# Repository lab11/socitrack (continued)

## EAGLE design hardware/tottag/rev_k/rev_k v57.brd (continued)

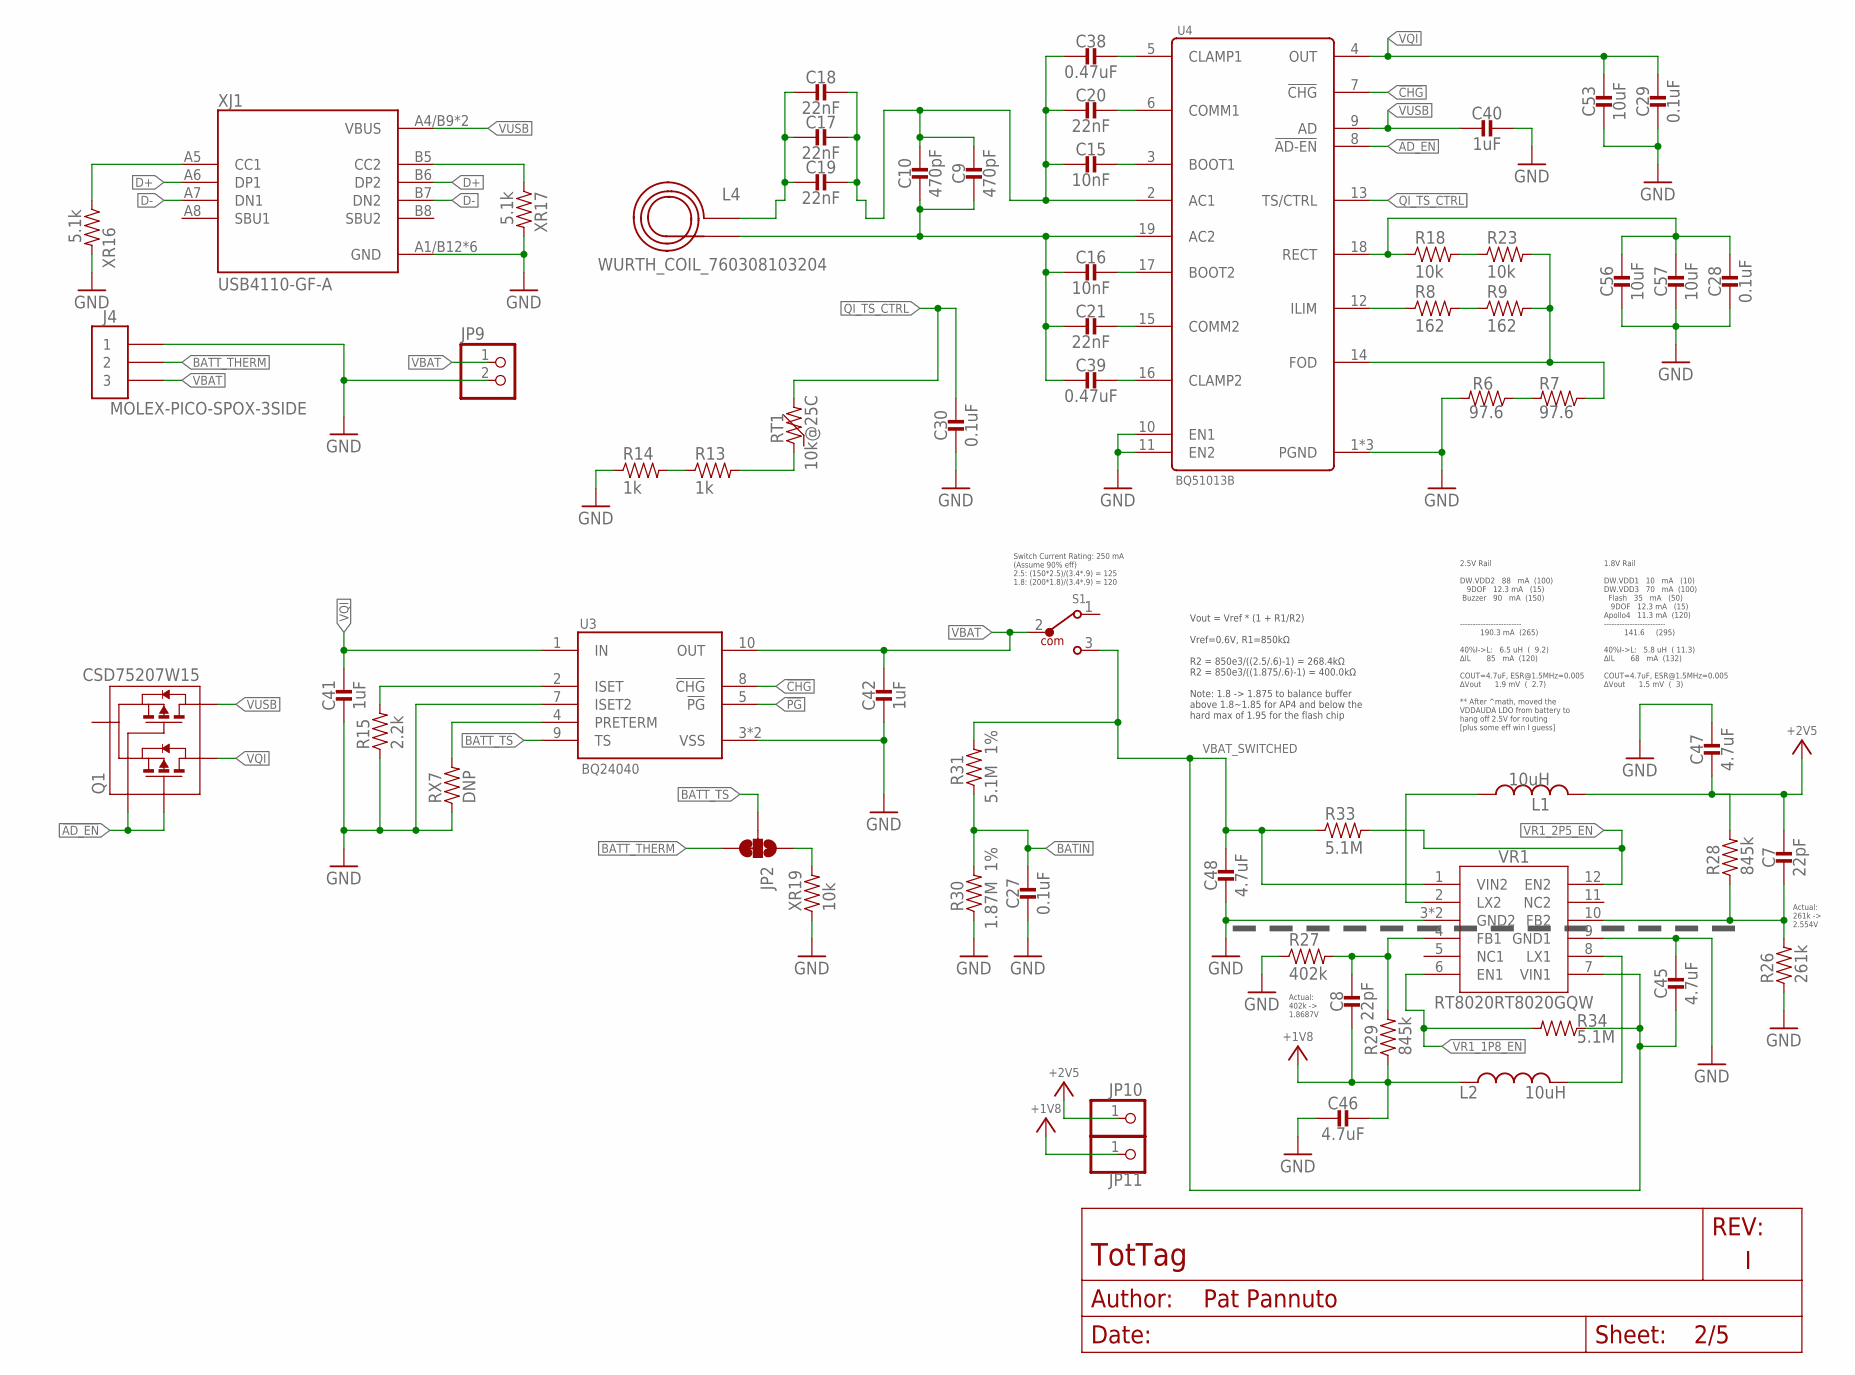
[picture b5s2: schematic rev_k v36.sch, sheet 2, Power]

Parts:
C7, C8: 22pF; 0201_CAP; MPN GRM0335C1H220FA01D
C9, C10: 470pF; 0402_CAP; MPN GRM1555C1H471JA01J; DIGIKEY 490-6242-1-ND
C15, C16: 10nF; 0402_CAP; MPN GRM155R71H103KA88J; DIGIKEY 490-6351-2-ND
C17, C18, C19: 22nF; 0402_CAP; MPN GRM155R71E223JA61D; DIGIKEY 490-10699-2-ND
C20, C21: 22nF; 0402_CAP; MPN CC0402ZRY5V8BB223; DIGIKEY 311-3823-1-ND
C27, C28, C29, C30: 0.1uF; 0402_CAP; MPN GRM155R71C104KA88J; DIGIKEY 490-6328-1-ND
C38, C39: 0.47uF; 0402_CAP; MPN GRT155R61E474ME01D; DIGIKEY 490-12270-1-ND
C40, C41, C42: 1uF; 0402_CAP; MPN GRM155R70J105KA12J
C45, C46, C47, C48: 4.7uF; 0603_CAP; MPN C1608X7S1A475K080AC
C53, C56, C57: 10uF; 0603_CAP; MPN CM105X5R106M25AT; DIGIKEY 1253-CM105X5R106M25ATCT-ND
J4: MOLEX-PICO-SPOX-3SIDE; MOLEX-PICO-SPOX-3_SIDE
JP2: JUMPER-SMT_3_1-NC_TRACE_SILK; SMT-JUMPER_3_1-NC_TRACE_SILK
JP9: PINHD-1X2; 1X02
JP10, JP11: PINHD-1X1; 1X01
L1, L2: 10uH; NRX3015; MPN NR3015T100M
L4: WURTH_COIL_760308103204
Q1: CSD75207W15; DSBGA
R6, R7: 97.6; 0402_RES; MPN RMCF0402FT97R6; DIGIKEY RMCF0402FT97R6CT-ND
R8, R9: 162; 0402_RES; MPN RMCF0402FT162R; DIGIKEY RMCF0402FT162RCT-ND
R13, R14: 1k; 0402_RES
R15: 2.2k; 0402_RES; MPN RMCF0402JT2K20; DIGIKEY RMCF0402JT2K20CT-ND
R18, R23: 10k; 0402_RES; MPN RC0402JR-0710KL; DIGIKEY 311-10KJRCT-ND
R26: 261k; 0201_RES; MPN ERJ-1GNF2613C
R27: 402k; 0201_RES; MPN ERJ-1GNF4023C
R28, R29: 845k; 0201_RES; MPN ERJ-1GNF8453C
R30: 1.87M; 0402_RES; TOLERANCE 1%; MPN RMCF0402FT1M87
R31: 5.1M; 0402_RES; TOLERANCE 1%; MPN RMCF0402FT5M10; DIGIKEY RMCF0402FT5M10CT-ND
R33, R34: 5.1M; 0402_RES; MPN RMCF0402FT5M10; DIGIKEY RMCF0402FT5M10CT-ND
RT1: 10k@25C; 0402_RES; MPN NCU15XH103F60RC; DIGIKEY 490-18149-1-ND
RX7: DNP; 0402_RES
S1: 450404015514; DIGIKEY 732-13665-1-ND
U3: BQ24040; DSQ0010A
U4: BQ51013B; RHL0020A
VR1: RT8020RT8020GQW; SON45P300X300X80-13T160X250N
XJ1: USB4110-GF-A; GCT_USB4110-GF-A
XR16, XR17: 5.1k; 0402_RES; MPN RMCF0402FT5K10; DIGIKEY RMCF0402FT5K10CT-ND
XR19: 10k; 0402_RES; MPN RC0402JR-0710KL; DIGIKEY 311-10KJRCT-ND

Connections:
!AD_EN: Q1.A1 (G1), Q1.C1 (G2), U4.8 (!AD-EN)
!CHG: U3.8 (!CHG), U4.7 (!CHG); also elsewhere on the board
!PG: U3.5 (!PG); also elsewhere on the board
+1V8: C8.P$2 (2), C46.1, JP11.1, L2.P$1 (1), R29.1; also elsewhere on the board
+2V5: C7.P$1 (1), C47.2, JP10.1, L1.P$2 (2), R28.2; also elsewhere on the board
BATIN: C27.1, R30.2, R31.1; also elsewhere on the board
BATT_THERM: J4.2, J4.2SUPP (2), JP2.3
BATT_TS: JP2.2, U3.9 (TS)
BQ_AC1: C9.1, C10.1, C15.2, C17.1, C18.1, C19.1, C20.2, C38.2, U4.2 (AC1)
BQ_AC2: C9.2, C10.2, C16.2, C21.2, C39.2, L4.P$2 (2), U4.19 (AC2)
BQ_BOOT1: C15.1, U4.3 (BOOT1)
BQ_BOOT2: C16.1, U4.17 (BOOT2)
BQ_CLAMP1: C38.1, U4.5 (CLAMP1)
BQ_CLAMP2: C39.1, U4.16 (CLAMP2)
BQ_COMM1: C20.1, U4.6 (COMM1)
BQ_COMM2: C21.1, U4.15 (COMM2)
BQ_FOD: R7.1, R9.2, R23.2, U4.14 (FOD)
BQ_ILM: R8.1, U4.12 (ILIM)
BQ_ISET: R15.2, U3.2 (ISET)
BQ_RECT: C28.1, C56.1, C57.1, R18.1, U4.18 (RECT)
COIL_AC1: C17.2, C18.2, C19.2, L4.P$1 (1)
D+: XJ1.A6 (DP1), XJ1.B6 (DP2)
D-: XJ1.A7 (DN1), XJ1.B7 (DN2)
GND: C27.2, C28.2, C29.2, C30.2, C40.1, C41.2, C42.2, C45.1, C46.2, C47.1, C48.2, C53.2, C56.2, C57.2, J4.1, J4.1SUPP (1), JP9.2, R6.2, R14.1, R15.1, R26.1, R27.1, R30.1, RX7.1, U3.3 (VSS), U3.7 (ISET2), U3.PAD (VSS), U4.1 (PGND), U4.10 (EN1), U4.11 (EN2), U4.20 (PGND), U4.PAD (PGND), VR1.3 (GND2), VR1.9 (GND1), VR1.13 (GND2), XJ1.A1/B12 (GND), XJ1.B1/A12 (GND), XJ1.S1 (GND), XJ1.S2 (GND), XJ1.S3 (GND), XJ1.S4 (GND), XR16.2, XR17.2, XR19.1; also elsewhere on the board
unnamed: XJ1.B5 (CC2), XR17.1
unnamed: XJ1.A5 (CC1), XR16.1
unnamed: R6.1, R7.2
unnamed: JP2.1, XR19.2
unnamed: RX7.2, U3.4 (PRETERM)
unnamed: R18.2, R23.1
unnamed: R8.2, R9.1
unnamed: R13.2, RT1.1
unnamed: R13.1, R14.2
QI_TS_CTRL: C30.1, RT1.2, U4.13 (TS/CTRL); also elsewhere on the board
VBAT: C42.1, J4.3, J4.3SUPP (3), JP9.1, S1.2, U3.10 (OUT)
VBAT_SWITCHED: C45.2, C48.1, R31.2, R33.1, R34.1, S1.3, VR1.1 (VIN2), VR1.7 (VIN1); also elsewhere on the board
VQI: C29.1, C41.1, C53.1, Q1.A2 (D1), Q1.A3 (D1), Q1.B3 (D1), U3.1 (IN), U4.4 (OUT)
VR1_1P8_EN: R34.2, VR1.6 (EN1)
VR1_2P5_EN: R33.2, VR1.12 (EN2)
VR1_FB1: C8.P$1 (1), R27.2, R29.2, VR1.4 (FB1)
VR1_FB2: C7.P$2 (2), R26.2, R28.1, VR1.10 (FB2)
VR1_LX1: L2.P$2 (2), VR1.8 (LX1)
VR1_LX2: L1.P$1 (1), VR1.2 (LX2)
VUSB: C40.2, Q1.B2 (D2), Q1.C2 (D2), Q1.C3 (D2), U4.9 (AD), XJ1.A4/B9 (VBUS), XJ1.B4/A9 (VBUS)

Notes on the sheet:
2.5V Rail DW.VDD2 88 mA (100) 9DOF 12.3 mA (15) Buzzer 90 mA (150) ------------------------ 190.3 mA (265) 40%I->L: 6.5 uH ( 9.2) ∆IL 85 mA (120) COUT=4.7uF, ESR@1.5MHz=0.005 ∆Vout 1.9 mV ( 2.7) ** After ^math, moved the VDDAUDA LDO from battery to hang off 2.5V for routing [plus some eff win I gue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
1.8V Rail DW.VDD1 10 mA (10) DW.VDD3 70 mA (100) Flash 35 mA (50) 9DOF 12.3 mA (15) Apollo4 11.3 mA (120) ------------------------ 141.6 (295) 40%I->L: 5.8 uH ( 11.3) ∆IL 68 mA (132) COUT=4.7uF, ESR@1.5MHz=0.005 ∆Vout 1.5 mV ( 3)
Vout = Vref * (1 + R1/R2) Vref=0.6V, R1=850kΩ R2 = 850e3/((2.5/.6)-1) = 268.4kΩ R2 = 850e3/((1.875/.6)-1) = 400.0kΩ Note: 1.8 -> 1.875 to balance buffer above 1.8~1.85 for AP4 and below the hard max of 1.95 for the flash chip
Switch Current Rating: 250 mA (Assume 90% eff) 2.5: (150*2.5)/(3.4*.9) = 125 1.8: (200*1.8)/(3.4*.9) = 120
Actual: 402k -> 1.8687V
Actual: 261k -> 2.554V

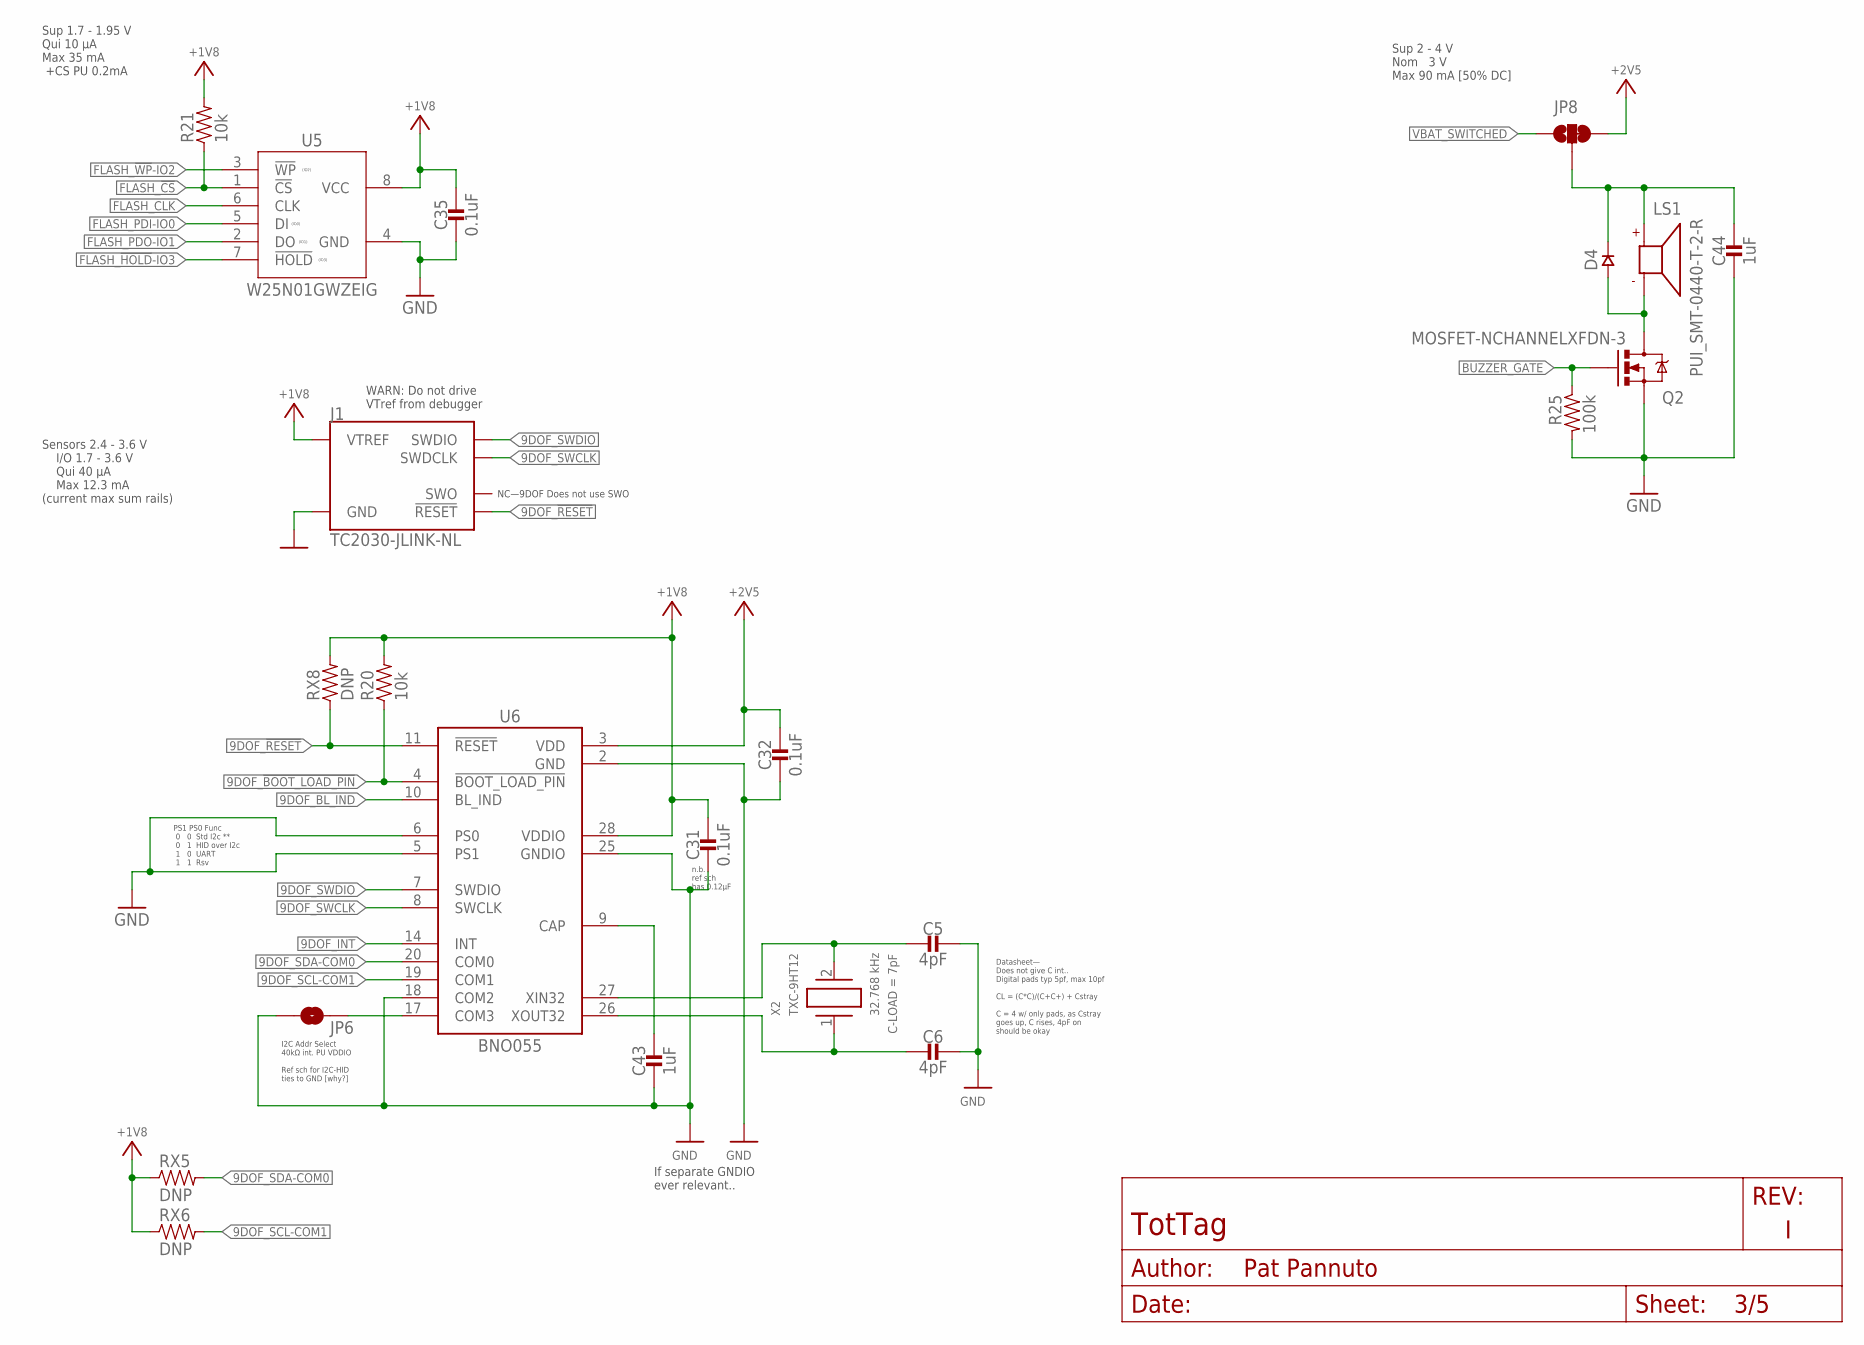
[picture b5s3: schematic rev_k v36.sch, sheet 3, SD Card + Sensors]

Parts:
C5, C6: 4pF; 0201_CAP; MPN GRM0335C1H4R0BA01D
C31, C32, C35: 0.1uF; 0402_CAP; MPN CL05A104KP5NNNC
C43, C44: 1uF; 0402_CAP; MPN GRM155R70J105KA12J
D4: DIODE0402; 0402_DIODE; MPN CDSQR400B-HF; DIGIKEY 641-2087-1-ND
J1: TC2030-JLINK-NL; TC2030-IDC-NL
JP6: JUMPER-SMT_2_NO_SILK; SMT-JUMPER_2_NO_SILK
JP8: JUMPER-SMT_3_1-NC_TRACE_SILK; SMT-JUMPER_3_1-NC_TRACE_SILK
LS1: PUI_SMT-0440-T-2-R; SMT-0440-T-2-R
Q2: MOSFET-NCHANNELXFDN-3; XFDFN-3
R20, R21: 10k; 0402_RES; MPN RC0402JR-0710KL; DIGIKEY 311-10KJRCT-ND
R25: 100k; 0402_RES; MPN RT0402BRE07100KL
RX5, RX6, RX8: DNP; 0603-RES
U5: W25N01GWZEIG; WSON127P800X600X80-9T430X340N
U6: BNO055; LGA28R0P510X4_5P2X3P8X1
X2: TXC-9HT12; MPN 9HT12-32.768KDZY-T

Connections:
9DOF_!BOOT_LOAD_PIN: R20.1, U6.4 (!BOOT_LOAD_PIN); also elsewhere on the board
9DOF_!RESET: J1.3 (!RESET), RX8.1, U6.11 (!RESET); also elsewhere on the board
9DOF_BL_IND: U6.10 (BL_IND); also elsewhere on the board
9DOF_CAP: C43.1, U6.9 (CAP)
9DOF_INT: U6.14 (INT); also elsewhere on the board
9DOF_SCL-COM1: RX6.2, U6.19 (COM1); also elsewhere on the board
9DOF_SDA-COM0: RX5.2, U6.20 (COM0); also elsewhere on the board
9DOF_SWCLK: J1.4 (SWDCLK), U6.8 (SWCLK)
9DOF_SWDIO: J1.2 (SWDIO), U6.7 (SWDIO)
9DOF_XI: C5.P$2 (2), U6.27 (XIN32), X2.2
9DOF_XO: C6.P$2 (2), U6.26 (XOUT32), X2.1
+1V8: C31.1, C35.1, J1.1 (VTREF), R20.2, R21.2, RX5.1, RX6.1, RX8.2, U5.8 (VCC), U6.28 (VDDIO); also elsewhere on the board
+2V5: C32.1, JP8.3, U6.3 (VDD); also elsewhere on the board
BUZZER_GATE: Q2.G, R25.1; also elsewhere on the board
BUZZER_SUPPLY: C44.1, D4.CATHODE, JP8.2, LS1.+
FLASH_!CS: R21.1, U5.1 (!CS); also elsewhere on the board
FLASH_!HOLD!-IO3: U5.7 (!HOLD); also elsewhere on the board
FLASH_!WP!-IO2: U5.3 (!WP); also elsewhere on the board
FLASH_CLK: U5.6 (CLK); also elsewhere on the board
FLASH_PDI-IO0: U5.5 (DI); also elsewhere on the board
FLASH_PDO-IO1: U5.2 (DO); also elsewhere on the board
GND: C5.P$1 (1), C6.P$1 (1), C31.2, C32.2, C35.2, C43.2, C44.2, J1.5 (GND), JP6.1, Q2.S, R25.2, U5.4 (GND), U6.2 (GND), U6.5 (PS1), U6.6 (PS0), U6.18 (COM2), U6.25 (GNDIO); also elsewhere on the board
unnamed: D4.ANODE, LS1.- (N), Q2.D
unnamed: JP6.2, U6.17 (COM3)
VBAT_SWITCHED: JP8.1; also elsewhere on the board

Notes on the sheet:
Sup 1.7 - 1.95 V Qui 10 µA Max 35 mA +CS PU 0.2mA
Sensors 2.4 - 3.6 V I/O 1.7 - 3.6 V Qui 40 µA Max 12.3 mA (current max sum rails)
Sup 2 - 4 V Nom 3 V Max 90 mA [50% DC]
PS1 PS0 Func 0 0 Std I2c ** 0 1 HID over I2c 1 0 UART 1 1 Rsv
If separate GNDIO ever relevant..
I2C Addr Select 40kΩ int. PU VDDIO Ref sch for I2C-HID ties to GND [why?]
n.b. ref sch has 0.12µF
WARN: Do not drive VTref from debugger
Datasheet— Does not give C int.. Digital pads typ 5pf, max 10pf CL = (C*C)/(C+C+) + Cstray C = 4 w/ only pads, as Cstray goes up, C rises, 4pF on should be okay
NC—9DOF Does not use SWO

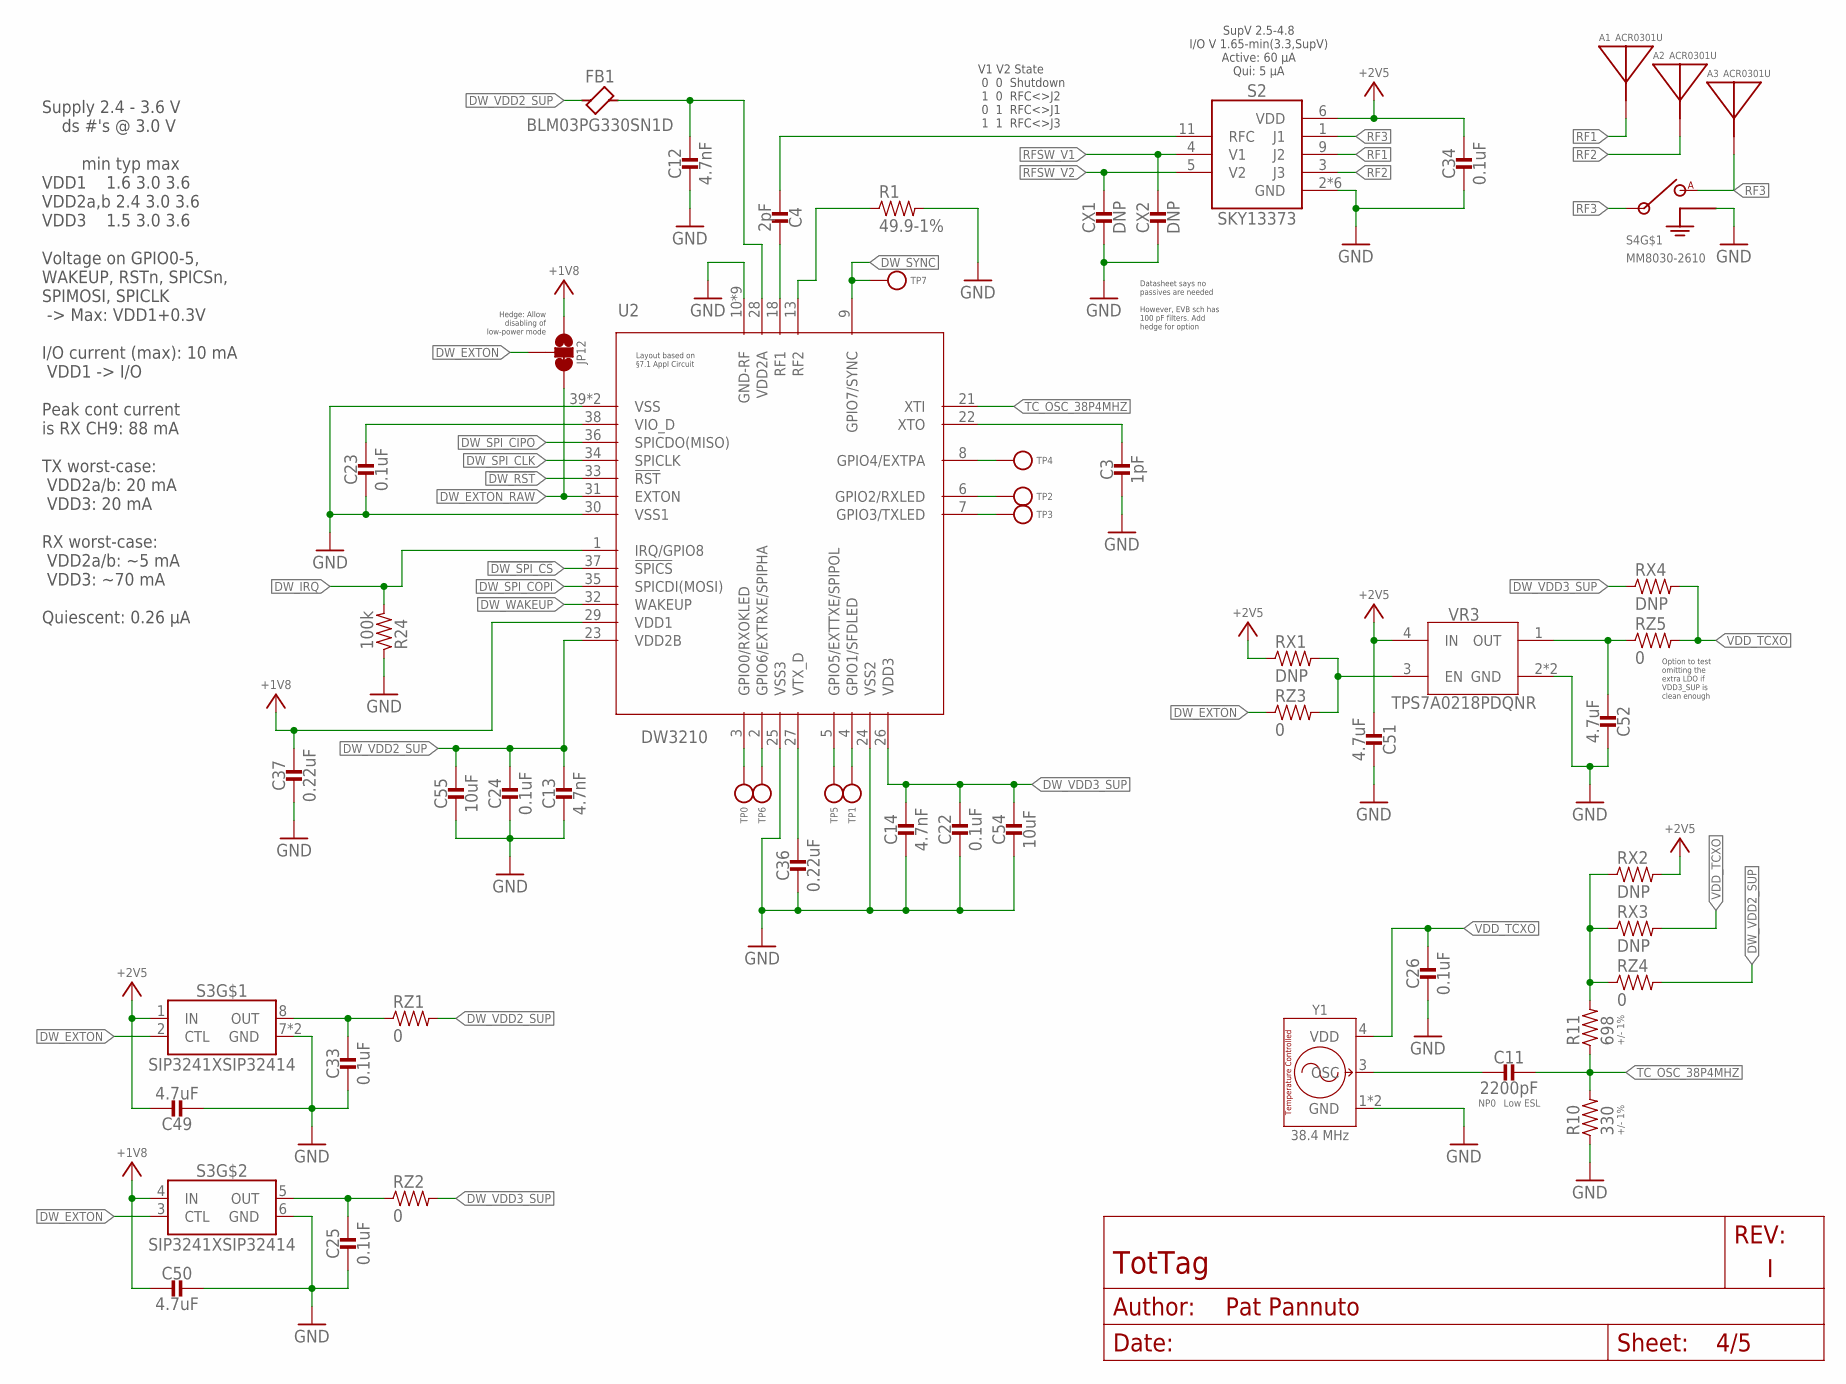
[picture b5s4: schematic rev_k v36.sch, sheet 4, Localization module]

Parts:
A1, A2, A3: ACR0301U
C3: 1pF; 0603_CAP; MPN C0603C109C5GACAUTO
C4: 2pF; 0201_CAP; MPN CBR02C209A5GAC
C11: 2200pF; 0603_CAP; MPN C0603C222F3GEC7867
C12, C13, C14: 4.7nF; 0402_CAP; MPN C0402C472K3RAC7867
C22, C23, C24, C25, C26, C33, C34: 0.1uF; 0402_CAP; MPN CL05A104KP5NNNC
C36, C37: 0.22uF; 0402_CAP; MPN CL05A224KP5NNNC
C49, C50, C51, C52: 4.7uF; 0603_CAP; MPN C1608X7S1A475K080AC
C54, C55: 10uF; 0603_CAP; MPN CM105X5R106M25AT; DIGIKEY 1253-CM105X5R106M25ATCT-ND
CX1, CX2: DNP; 0603_CAP
FB1: BLM03PG330SN1D; 0201_FB; MPN BLM03PG330SN1D
JP12: JUMPER-SMT_3_1-NC_TRACE_SILK; SMT-JUMPER_3_1-NC_TRACE_SILK
R1: 49.9-1%; 0201_RES; MPN ERJ-1GNF49R9C
R10: 330; 0603-RES; TOLERANCE +/- 1%; MPN RC0805FR-13330RL
R11: 698; 0603-RES; TOLERANCE +/- 1%; MPN RC0805FR-07698RL
R24: 100k; 0402_RES; MPN RT0402BRE07100KL
RX1, RX2, RX3, RX4: DNP; 0603-RES
RZ1, RZ2, RZ3, RZ4, RZ5: 0; 0603-RES; MPN RMCF0603ZT0R00
S2: SKY13373
S3: SIP3241XSIP32414; TDFN2X2X0P6-8
S4: MM8030-2610
TP0, TP1, TP2, TP3, TP4, TP5, TP6, TP7: TEST-POINT; PAD.03X.03
U2: DW3210; QFN40P500X500X80-40N
VR3: TPS7A0218PDQNR; 4-XDFN-EP
Y1: 38.4 MHz; OSCCC200X160X80; MPN O 38,40-JT21G-E-M-1,8-LF

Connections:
!DW_RST: U2.33 (!RST); also elsewhere on the board
!DW_SPI_CS: U2.37 (!SPICS); also elsewhere on the board
+1V8: C37.1, C50.2, JP12.1, S3.4 (IN), U2.29 (VDD1); also elsewhere on the board
+2V5: C34.1, C49.1, C51.2, RX1.1, RX2.2, S2.6 (VDD), S3.1 (IN), VR3.4 (IN); also elsewhere on the board
DW_EXTON: JP12.2, RZ3.1, S3.2 (CTL), S3.3 (CTL)
DW_EXTON_RAW: JP12.3, U2.31 (EXTON)
DW_GPIO4: TP4.P$1, U2.8 (GPIO4/EXTPA)
DW_GPIO5: TP5.P$1, U2.5 (GPIO5/EXTTXE/SPIPOL)
DW_GPIO6: TP6.P$1, U2.2 (GPIO6/EXTRXE/SPIPHA)
DW_IRQ: R24.2, U2.1 (IRQ/GPIO8); also elsewhere on the board
DW_RF1: C4.P$1 (1), U2.18 (RF1)
DW_RF2: R1.1, U2.13 (RF2)
DW_RXLED: TP2.P$1, U2.6 (GPIO2/RXLED)
DW_RXOKLED: TP0.P$1, U2.3 (GPIO0/RXOKLED)
DW_SFDLED: TP1.P$1, U2.4 (GPIO1/SFDLED)
DW_SPI_CIPO: U2.36 (SPICDO(MISO)); also elsewhere on the board
DW_SPI_CLK: U2.34 (SPICLK); also elsewhere on the board
DW_SPI_COPI: U2.35 (SPICDI(MOSI)); also elsewhere on the board
DW_SYNC: TP7.P$1, U2.9 (GPIO7/SYNC)
DW_TXLED: TP3.P$1, U2.7 (GPIO3/TXLED)
DW_VDD2A: C12.1, FB1.P$2, U2.28 (VDD2A)
DW_VDD2_PWROUT: C33.1, RZ1.1, S3.8 (OUT)
DW_VDD2_SUP: C13.1, C24.1, C55.1, FB1.P$1, RZ1.2, RZ4.2, U2.23 (VDD2B)
DW_VDD3_PWROUT: C25.1, RZ2.1, S3.5 (OUT)
DW_VDD3_SUP: C14.1, C22.1, C54.1, RX4.1, RZ2.2, U2.26 (VDD3)
DW_VIO_D: C23.1, U2.38 (VIO_D)
DW_VTX_D: C36.1, U2.27 (VTX_D)
DW_WAKEUP: U2.32 (WAKEUP); also elsewhere on the board
DW_XTO: C3.1, U2.22 (XTO)
GND: C3.2, C12.2, C13.2, C14.2, C22.2, C23.2, C24.2, C25.2, C26.2, C33.2, C34.2, C36.2, C37.2, C49.2, C50.1, C51.1, C52.1, C54.2, C55.2, CX1.2, CX2.2, R1.2, R10.1, R24.1, S2.2 (GND), S2.7 (GND), S2.8 (GND), S2.10 (GND), S2.12 (GND), S2.PAD (GND), S3.6 (GND), S3.7 (GND), S3.PAD (GND), S4.G1 (GND), S4.G2 (GND), U2.10 (GND-RF), U2.11 (GND-RF), U2.12 (GND-RF), U2.14 (GND-RF), U2.15 (GND-RF), U2.16 (GND-RF), U2.17 (GND-RF), U2.19 (GND-RF), U2.20 (GND-RF), U2.24 (VSS2), U2.25 (VSS3), U2.30 (VSS1), U2.39 (VSS), U2.40 (VSS), VR3.2 (GND), VR3.PAD (GND), Y1.1 (GND), Y1.2 (GND); also elsewhere on the board
RF1: A1.FEED, S2.9 (J2)
RF2: A2.FEED, S2.3 (J3)
RF3: A3.FEED, S2.1 (J1), S4.IN, S4.OUT (A)
RFC: C4.P$2 (2), S2.11 (RFC)
RFSW_V1: CX2.1, S2.4 (V1); also elsewhere on the board
RFSW_V2: CX1.1, S2.5 (V2); also elsewhere on the board
TCXO_BIAS_SUPP: R11.2, RX2.1, RX3.1, RZ4.1
TCXO_OUT: C11.2, Y1.3 (OSC)
TCXO_REG_EN: RX1.2, RZ3.2, VR3.3 (EN)
TCXO_REG_OUT: C52.2, RZ5.1, VR3.1 (OUT)
TC_OSC_38P4MHZ: C11.1, R10.2, R11.1, U2.21 (XTI)
VDD_TCXO: C26.1, RX3.2, RX4.2, RZ5.2, Y1.4 (VDD)

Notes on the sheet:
Supply 2.4 - 3.6 V ds #'s @ 3.0 V min typ max VDD1 1.6 3.0 3.6 VDD2a,b 2.4 3.0 3.6 VDD3 1.5 3.0 3.6 Voltage on GPIO0-5, WAKEUP, RSTn, SPICSn, SPIMOSI, SPICLK -> Max: VDD1+0.3V I/O current (max): 10 mA VDD1 -> I/O Peak cont current is RX CH9: 88 mA TX worst-case: VDD2a/b: 20 mA VDD3: 20 mA RX worst-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
SupV 2.5-4.8 I/O V 1.65-min(3.3,SupV) Active: 60 µA Qui: 5 µA
V1 V2 State 0 0 Shutdown 1 0 RFC<>J2 0 1 RFC<>J1 1 1 RFC<>J3
Datasheet says no passives are needed However, EVB sch has 100 pF filters. Add hedge for option
Hedge: Allow disabling of low-power mode
Option to test omitting the extra LDO if VDD3_SUP is clean enough

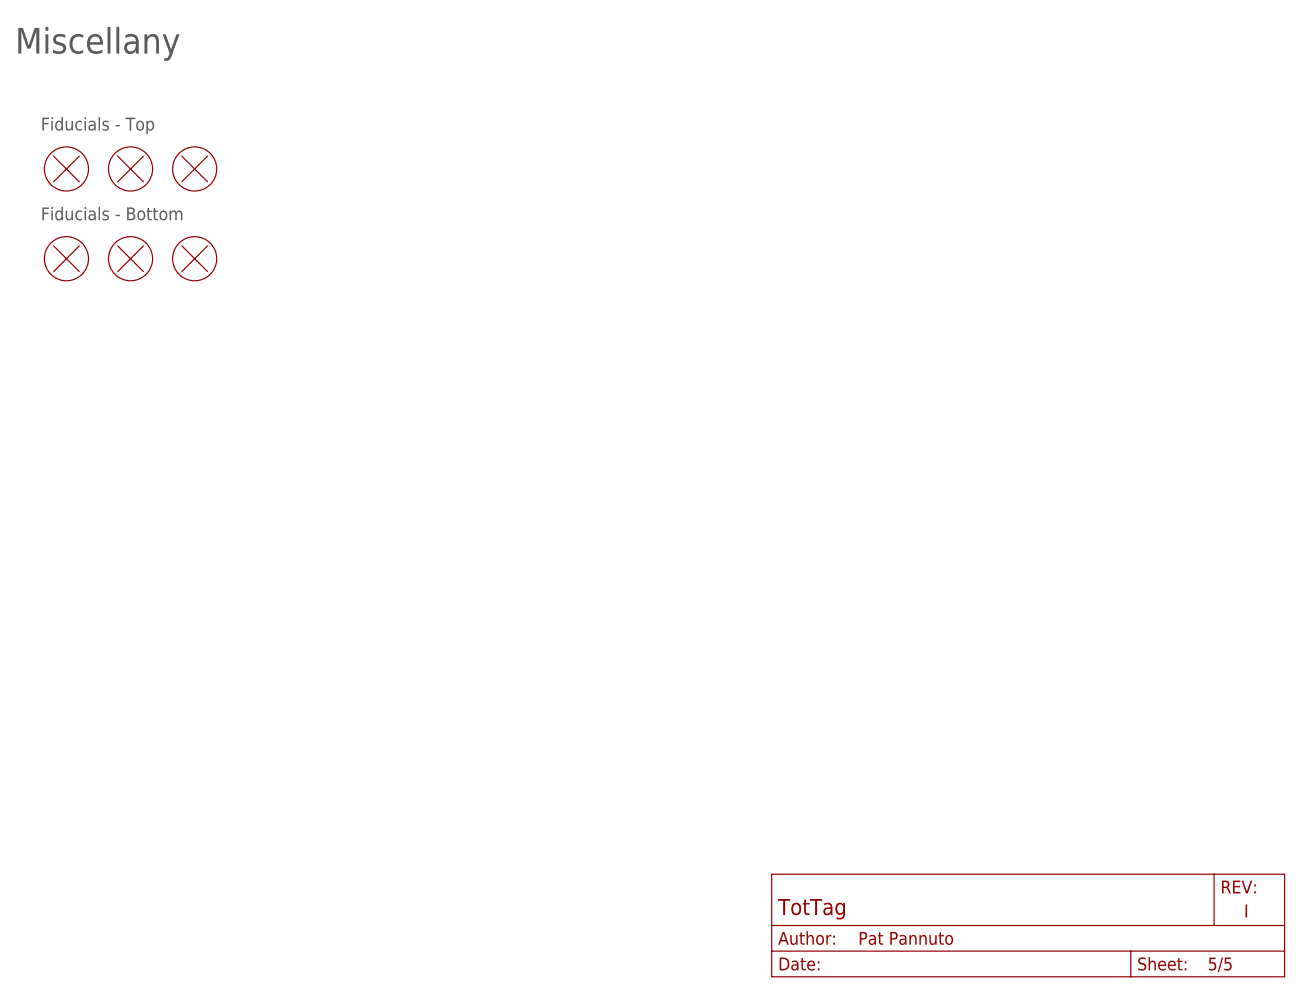
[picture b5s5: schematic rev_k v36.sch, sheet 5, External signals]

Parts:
FD1, FD2, FD3, FD4, FD5, FD6: FIDUCIAL; FIDUCIAL_1MM-CU_2MM-MASK

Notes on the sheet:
Miscellany
Fiducials - Top
Fiducials - Bottom

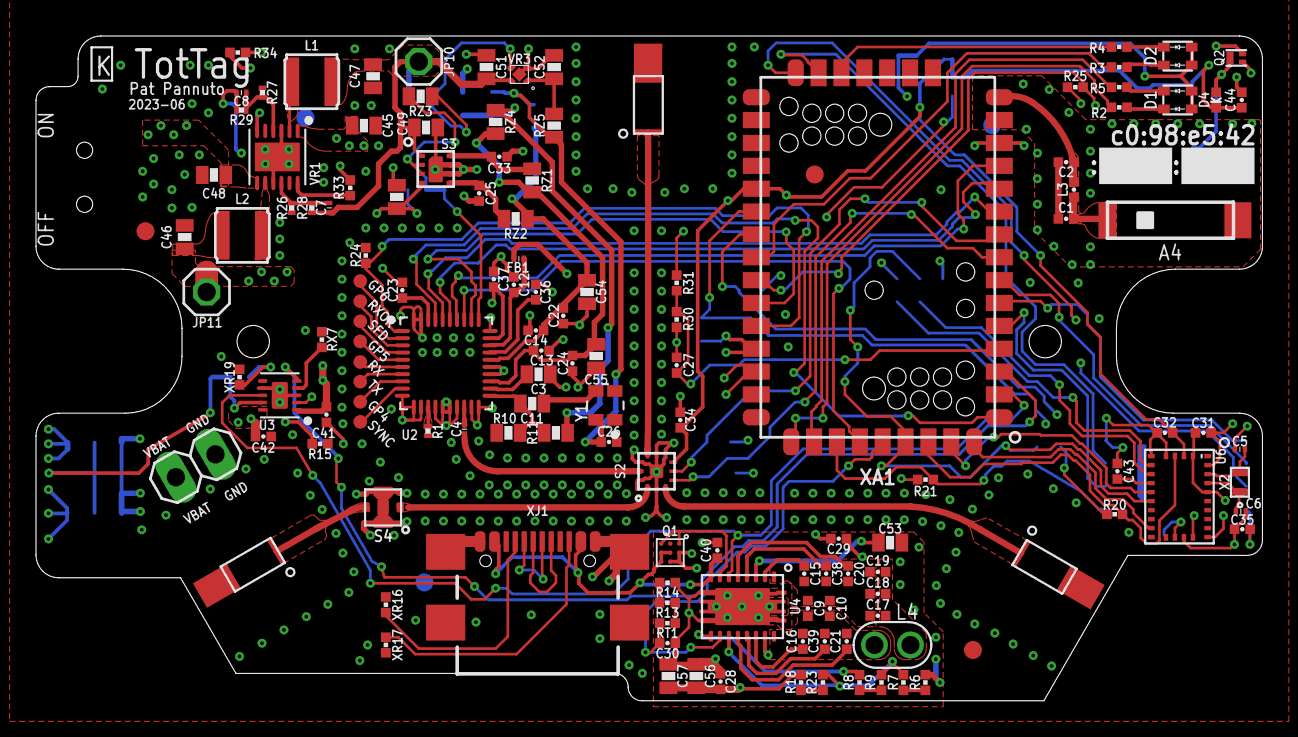
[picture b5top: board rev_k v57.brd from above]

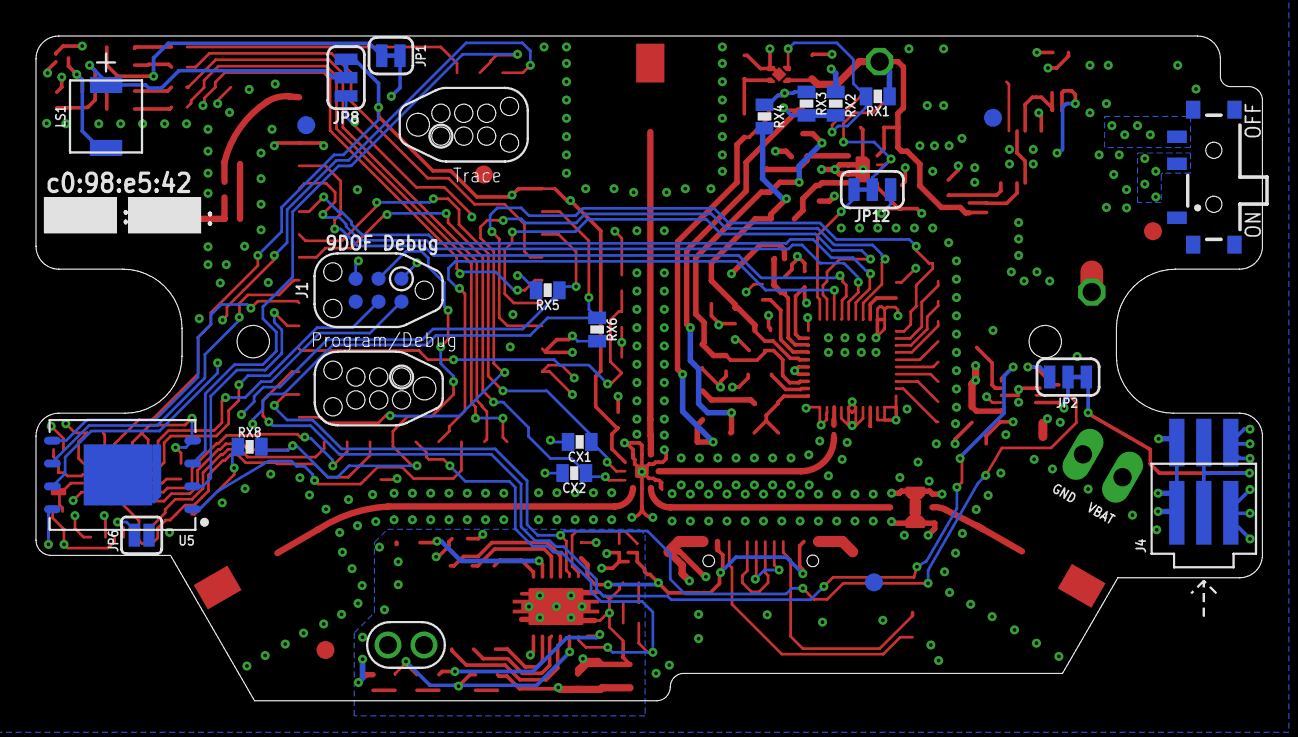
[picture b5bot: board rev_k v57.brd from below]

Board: 4 copper layers, 68.1 x 36.9 mm, 158 parts (22 on the bottom side), 116 nets.
